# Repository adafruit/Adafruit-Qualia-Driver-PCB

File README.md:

## Adafruit Qualia Driver PCB

<a href="http://www.adafruit.com/products/1716"><br/>
Click here to purchase one from the Adafruit shop</a>

PCB files for the Adafruit Qualia Driver. Format is EagleCAD schematic and board layout
* https://www.adafruit.com/product/1716

### DESCRIPTION
The Qualia Retina driver board is a work of art (it was designed by resident engineer KTOWN). It's used in the Adafruit Qualia 9.7" DisplayPort Monitor Kit and we use the really awesome LT3754 as a 12-channel constant current driver with individual backlight string channel control. This gives the backlight perfect consistency over any usage or temperature range. A ATtiny85 handles the backlight dimming and soft on/off, so you can PWM the backlight over a range to get the look you want.

This driver is available for advanced users only! The Molex connector that is used to connect to the LG display is insanely delicate and breaks very very very easily if you are not very careful! If you order this driver board and break the connector, it may no longer work and we cannot repair it. If you break it you may have to buy another driver. We do not offer any returns, refunds or replacements! Do not purchase if you are not comfortable with this risk!

### License

Adafruit invests time and resources providing this open source design, please support Adafruit and open-source hardware by purchasing products from [Adafruit.com](https://www.adafruit.com)!

Designed by Adafruit Industries. 

Creative Commons Attribution, Share-Alike license, check license.txt for more information All text above must be included in any redistribution - see license.txt for more information.

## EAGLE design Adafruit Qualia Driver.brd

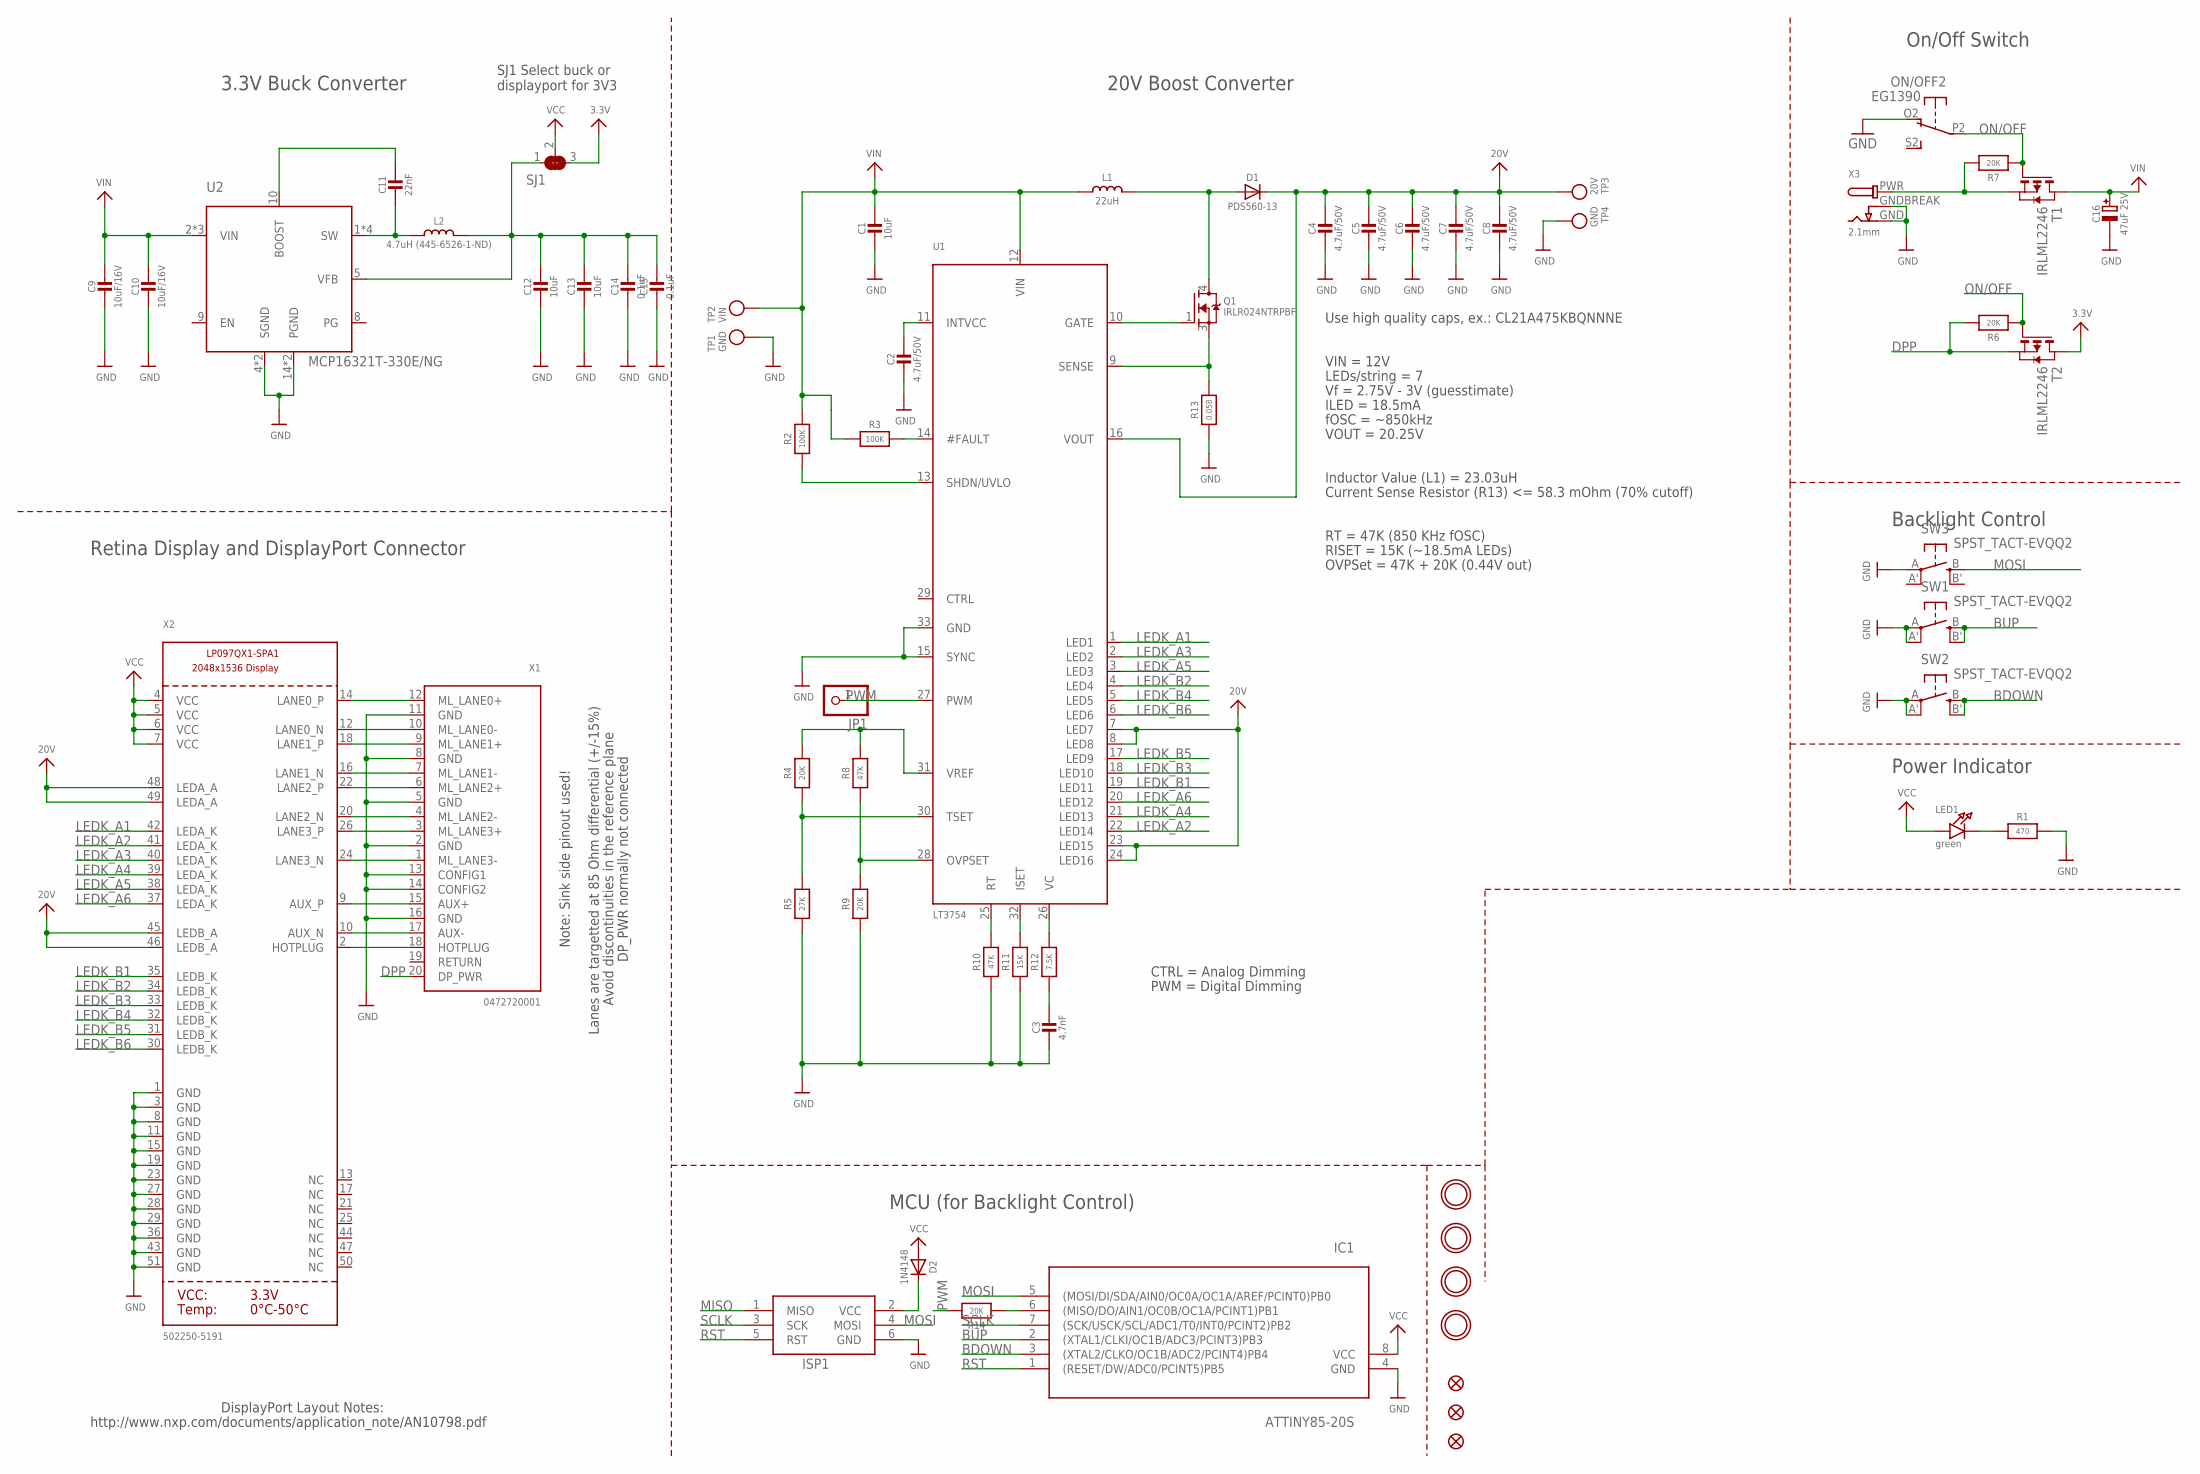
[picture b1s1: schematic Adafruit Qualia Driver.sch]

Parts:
C1, C12, C13: 10uF; _0805
C2, C4, C5, C6, C7, C8: 4.7uF/50V; _0805
C3: 4.7nF; _0805
C9, C10: 10uF/16V; _0805
C11: 22nF; _0805
C14, C15: 0.1uF; _0805
C16: 47uF 25V; PANASONIC_C
D1: PDS560-13; POWERDI-5
D2: 1N4148; SOD-323
FID1, FID2, FID3: FIDUCIAL""; FIDUCIAL_1MM
IC1: ATTINY85-20S; SOIC8
ISP1: AVRISP-6; AVRISP
JP1: PINHD-1X1CB; 1X01-CLEANBIG
L1: 22uH; INDUCTOR_6X6MM_SUMIDA_CDRH5D28
L2: 4.7uH (445-6526-1-ND); INDUCTOR_5X5MM_TDK_VLC5045
LED1: green; CHIPLED_0805
ON/OFF: EG1390
Q1: IRLR024NTRPBF; DPAK
R1: 470; _0805
R2, R3: 100K; _0805
R4, R9, R14: 20K; _0805
R5: 27K; _0805
R6, R7: 20K; _0805MP
R8, R10: 47K; _0805
R11: 15K; _0805
R12: 7.5K; _0805
R13: 0.058; 2512
SJ1: SOLDERJUMPER_2WAY; SOLDERJUMPER_2WAY_OPEN_NOPASTE
SW1, SW2, SW3: SPST_TACT-EVQQ2; EVQ-Q2
T1, T2: IRLML2246; SOT-23
TP1, TP4: GND; TESTPOINT_ROUND_1MM
TP2: VIN; TESTPOINT_ROUND_1MM
TP3: 20V; TESTPOINT_ROUND_1MM
U1: LT3754; QFN32_5MM
U2: MCP16321T-330E/NG; QFN16_3MM
U$11, U$32, U$33, U$34: MOUNTINGHOLE3.0THIN; MOUNTINGHOLE_3.0_PLATEDTHIN
X1: 0472720001; DISPLAYPORT_0472720001
X2: 502250-5191; FPC_51PIN_502250-5191_EXT
X3: 2.1mm; DCJACK_2MM_SMT

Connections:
3.3V: SJ1.3, T2.1 (D)
20V: C4.1, C5.1, C6.1, C7.1, C8.1, D1.C, TP3.P$1, U1.7 (LED7), U1.8 (LED8), U1.16 (VOUT), U1.23 (LED15), U1.24 (LED16), X2.45 (LEDB_A), X2.46 (LEDB_A), X2.48 (LEDA_A), X2.49 (LEDA_A)
AUX+: X1.15 (AUX+), X2.9 (AUX_P)
AUX-: X1.17 (AUX-), X2.10 (AUX_N)
BDOWN: IC1.3 ((XTAL2/CLKO/OC1B/ADC2/PCINT4)PB4), SW2.B (S), SW2.B' (S1)
BUP: IC1.2 ((XTAL1/CLKI/OC1B/ADC3/PCINT3)PB3), SW1.B (S), SW1.B' (S1)
DPP: R6.2, T2.2 (S), X1.20 (DP_PWR)
GND: C1.2, C2.2, C3.2, C4.2, C5.2, C6.2, C7.2, C8.2, C9.2, C10.2, C12.2, C13.2, C14.2, C15.2, C16.-, IC1.4 (GND), ISP1.6 (GND), ON/OFF.O2 (O), R1.2, R5.1, R9.1, R10.1, R11.1, R13.1, SW1.A, SW1.A' (P1), SW2.A, SW2.A' (P1), SW3.A, TP1.P$1, TP4.P$1, U1.15 (SYNC), U1.33 (GND), U2.4 (SGND), U2.14 (PGND), U2.15 (PGND), U2.THERMAL (SGND), X1.2 (GND), X1.5 (GND), X1.8 (GND), X1.11 (GND), X1.13 (CONFIG1), X1.14 (CONFIG2), X1.16 (GND), X2.1 (GND), X2.3 (GND), X2.8 (GND), X2.11 (GND), X2.15 (GND), X2.19 (GND), X2.23 (GND), X2.27 (GND), X2.28 (GND), X2.29 (GND), X2.36 (GND), X2.43 (GND), X2.51 (GND), X3.GND, X3.GNDBREAK
HOTPLUG: X1.18 (HOTPLUG), X2.2 (HOTPLUG)
LEDK_A1: U1.1 (LED1), X2.42 (LEDA_K)
LEDK_A2: U1.22 (LED14), X2.41 (LEDA_K)
LEDK_A3: U1.2 (LED2), X2.40 (LEDA_K)
LEDK_A4: U1.21 (LED13), X2.39 (LEDA_K)
LEDK_A5: U1.3 (LED3), X2.38 (LEDA_K)
LEDK_A6: U1.20 (LED12), X2.37 (LEDA_K)
LEDK_B1: U1.19 (LED11), X2.35 (LEDB_K)
LEDK_B2: U1.4 (LED4), X2.34 (LEDB_K)
LEDK_B3: U1.18 (LED10), X2.33 (LEDB_K)
LEDK_B4: U1.5 (LED5), X2.32 (LEDB_K)
LEDK_B5: U1.17 (LED9), X2.31 (LEDB_K)
LEDK_B6: U1.6 (LED6), X2.30 (LEDB_K)
MISO: IC1.6 ((MISO/DO/AIN1/OC0B/OC1A/PCINT1)PB1), ISP1.1 (MISO), R14.1
MOSI: IC1.5 ((MOSI/DI/SDA/AIN0/OC0A/OC1A/AREF/PCINT0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), ISP1.4 (MOSI), SW3.B (S)
unnamed: X1.12 (ML_LANE0+), X2.14 (LANE0_P)
unnamed: X1.10 (ML_LANE0-), X2.12 (LANE0_N)
unnamed: X1.9 (ML_LANE1+), X2.18 (LANE1_P)
unnamed: X1.7 (ML_LANE1-), X2.16 (LANE1_N)
unnamed: X1.6 (ML_LANE2+), X2.22 (LANE2_P)
unnamed: X1.4 (ML_LANE2-), X2.20 (LANE2_N)
unnamed: X1.3 (ML_LANE3+), X2.26 (LANE3_P)
unnamed: X1.1 (ML_LANE3-), X2.24 (LANE3_N)
unnamed: C2.1, U1.11 (INTVCC)
unnamed: R2.1, U1.13 (SHDN/UVLO)
unnamed: R3.2, U1.14 (#FAULT)
unnamed: R12.2, U1.26 (VC)
unnamed: C3.1, R12.1
unnamed: LED1.C, R1.1
unnamed: R4.1, R5.2, U1.30 (TSET)
unnamed: R4.2, R8.2, U1.31 (VREF)
unnamed: R7.2, T1.2 (S), X3.PWR
unnamed: R8.1, R9.2, U1.28 (OVPSET)
unnamed: R10.2, U1.25 (RT)
unnamed: D2.C, ISP1.2 (VCC)
unnamed: R11.2, U1.32 (ISET)
unnamed: Q1.3 (S), R13.2, U1.9 (SENSE)
unnamed: Q1.1 (G), U1.10 (GATE)
unnamed: D1.A1 (A), D1.A2 (A), L1.P$2 (2), Q1.4 (D)
unnamed: C12.1, C13.1, C14.1, C15.1, L2.P$2 (2), SJ1.1, U2.5 (VFB)
unnamed: C11.1, U2.10 (BOOST)
unnamed: C11.2, L2.P$1 (1), U2.1 (SW), U2.12 (SW), U2.13 (SW), U2.16 (SW)
ON/OFF: ON/OFF.P2, R6.1, R7.1, T1.3 (G), T2.3 (G)
PWM: JP1.1, R14.2, U1.27 (PWM)
RST: IC1.1 ((RESET/DW/ADC0/PCINT5)PB5), ISP1.5 (RST)
SCLK: IC1.7 ((SCK/USCK/SCL/ADC1/T0/INT0/PCINT2)PB2), ISP1.3 (SCK)
VCC: D2.A, IC1.8 (VCC), LED1.A, SJ1.2, X2.4 (VCC), X2.5 (VCC), X2.6 (VCC), X2.7 (VCC)
VIN: C1.1, C9.1, C10.1, C16.+, L1.P$1 (1), R2.2, R3.1, T1.1 (D), TP2.P$1, U1.12 (VIN), U2.2 (VIN), U2.3 (VIN), U2.11 (VIN)

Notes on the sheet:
Note: Sink side pinout used!
DP_PWR normally not connected
Lanes are targetted at 85 Ohm differential (+/-15%)
Avoid discontinuities in the reference plane
DisplayPort Layout Notes:
http://www.nxp.com/documents/application_note/AN10798.pdf
Use high quality caps, ex.: CL21A475KBQNNNE
Inductor Value (L1) = 23.03uH
VIN = 12V
LEDs/string = 7
Vf = 2.75V - 3V (guesstimate)
ILED = 18.5mA
VOUT = 20.25V
fOSC = ~850kHz
Current Sense Resistor (R13) <= 58.3 mOhm (70% cutoff)
RT = 47K (850 KHz fOSC)
RISET = 15K (~18.5mA LEDs)
OVPSet = 47K + 20K (0.44V out)
20V Boost Converter
MCU (for Backlight Control)
On/Off Switch
Retina Display and DisplayPort Connector
3.3V Buck Converter
CTRL = Analog Dimming
PWM = Digital Dimming
Backlight Control
Power Indicator
SJ1 Select buck or displayport for 3V3

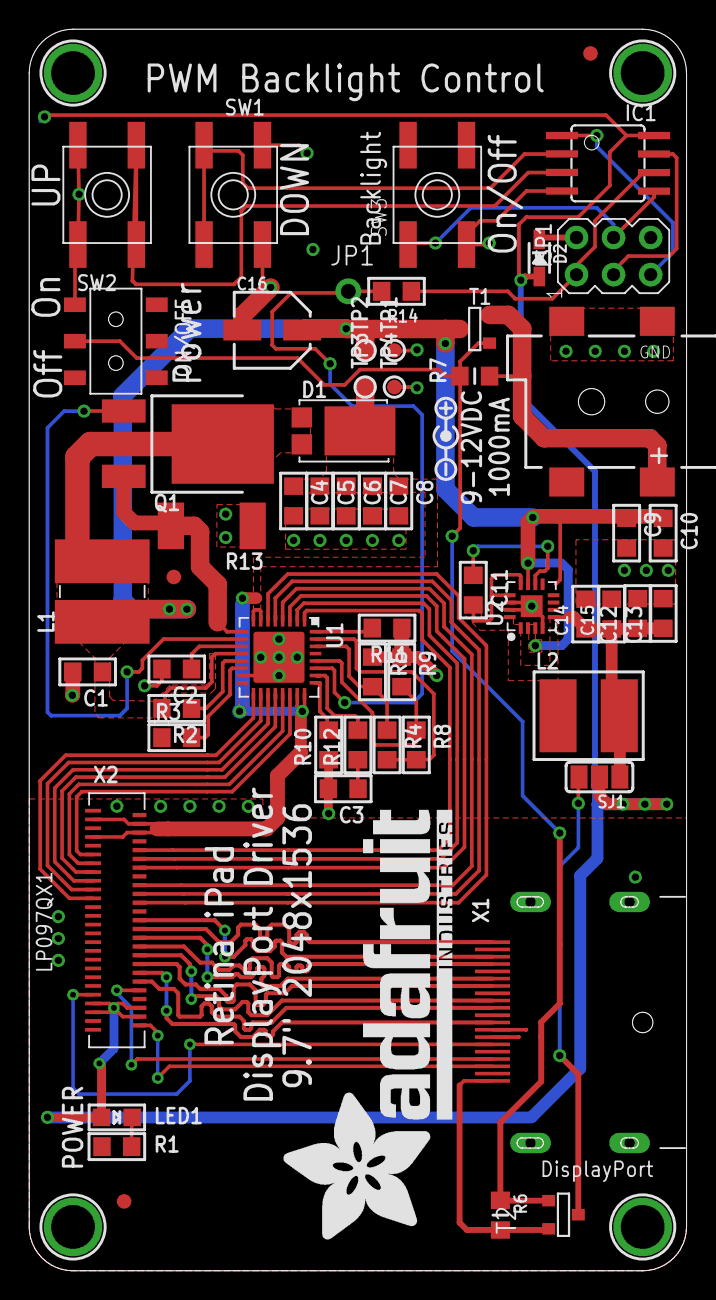
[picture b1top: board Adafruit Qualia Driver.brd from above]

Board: 2 copper layers, 45.0 x 85.0 mm, 64 parts (0 on the bottom side), 56 nets.

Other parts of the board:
U$10: SYMBOL_POSITIVE_CENTER-M
U$39: ADAFRUIT_TEXT_30MM

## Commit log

2016-09-28 init
2016-09-28 right version

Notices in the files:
parts and their libraries:
microbuilder: This work is placed in the public domain, and may be freely used for commercial and non-commercial work with the following conditions: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
